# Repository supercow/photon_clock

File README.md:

# Photon Clock

This repository contains all of the software and schematics required to build
and flash a 16x2 smart clock driven by a [Particle Photon](https://store.particle.io/#photon).

## Parts list

- PCB (see below for details)
- [HD44780 assembled LCD](https://www.adafruit.com/products/1447)
- Trim potentiometer (should come with the HD44780)
- [TMP36 temperature sensor](https://www.adafruit.com/products/165) (not needed if using external weather)
- [Particle Photon with headers](https://store.particle.io/#photon)
- ~50-60ohm THT resistor
- 10nF capacitor

### 3D printed enclosure
- Enclosure itself (see below for details)
- 4x M2x20mm machine screws
- 4x M2 nuts
- [Optional] 30mm cooling fan (requires fasteners and electrical tape)
- [Optional] Self-adhesive velcro strips

## PCB details

Eagle 8 format schematics are included in the "eagle" directory in this
repository. If you wish to order a PCB, you will need to use a service that
supports Eagle .brd files, or generate your own Gerbers.

I recommend [OSH Park](https://www.oshpark.com/) for ease of use, cost, quality,
and their cool purple soldermask. You can order this board directly with [this](https://www.oshpark.com/orders/cart)
link.

## 3D printed enclosure details

Autodesk Fusion 360 source files and printable STL files are included in the "enclosure" directory in this repository.

### Assembly notes
* Print using 100% infill; no supports necessary.
* If using a cooling fan, cover the top of the partition that separates the Photon board from the temperature sensor with electrical tape. This will create a seal between the enclosure bottom and the PCB to block pushed air from impacting temperature readings. Fan is intended to be mounted externally using the mounting holes on the enclosure bottom.
* Enclosure is intended to be mounted under a computer monitor with velcro but works just fine unmounted. Velcro should be adhered to the enclosure side without the honeycomb cutouts.

## Building the software

### Pre-requisites

- A registered, Wi-Fi enabled Photon, ideally already connected
- The Particle IDE or command line tools installed and configured
- If you wish to use the command line version, a \*nix compatible shell is
  required

See instructions in the `code/build.sh` script to build and flash the Photon via
the command line. To flash via the Particle Atom IDE, open the project in `code`
and flash as usual.

If you wish to use the built-in temperature sensor, you will need to comment out
the following line:

`#define EXTERNAL_TEMP true`

## External integrations

In order for the clock to set the correct timezone, you will need to configure
the `timezone.json` external integration in the `integrations` directory in the
Particle console.

In order for the clock to collect external weather, you will need to configure
the `weather.json` external integration.

**Please note** that you must supply your own API key or none of the
integrations will work.

To configure each custom integration:
1. Go to [https://console.particle.io/integrations](https://console.particle.io/integrations) in your web browser
1. Click "NEW INTEGRATION"
1. Click "Webhook", then "Custom JSON"
1. Paste the contents of the relevant `.json` file from the `integrations`
   directory
1. Edit the URL section to include your API key
1. Click "CREATE WEBHOOK"

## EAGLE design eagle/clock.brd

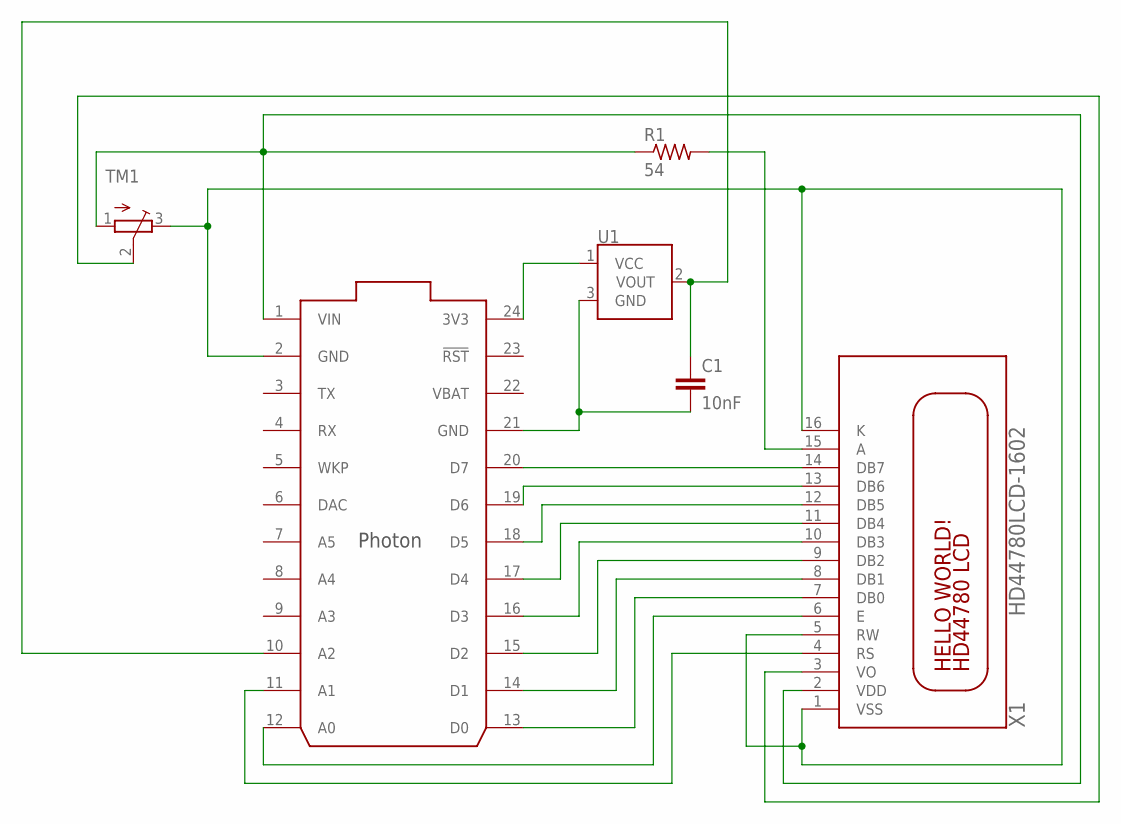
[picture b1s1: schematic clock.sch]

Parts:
C1: 10nF; CAP-PTH-10MM
R1: 54; 0309/12
TM1: TRIMPOT3386; TRIM-3386
U1: TMP36GT9; TO-92
U$1: PHOTON_WITH_HEADERS; PHOTON
X1: HD44780LCD-1602; LCD1602

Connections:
unnamed: U$1.19 (D6), X1.13 (DB6)
unnamed: C1.1, U1.2 (VOUT), U$1.10 (A2)
unnamed: U$1.12 (A0), X1.6 (E)
unnamed: U$1.18 (D5), X1.12 (DB5)
unnamed: U$1.17 (D4), X1.11 (DB4)
unnamed: U$1.20 (D7), X1.14 (DB7)
unnamed: U$1.16 (D3), X1.10 (DB3)
unnamed: U$1.15 (D2), X1.9 (DB2)
unnamed: U$1.14 (D1), X1.8 (DB1)
unnamed: U$1.13 (D0), X1.7 (DB0)
unnamed: U$1.11 (A1), X1.4 (RS)
unnamed: R1.2, X1.15 (A)
unnamed: TM1.2 (S), X1.3 (VO)
unnamed: U1.1 (VCC), U$1.24 (3V3)
unnamed: C1.2, U1.3 (GND), U$1.21 (GND)
VBAT: U$1.22 (VBAT)
VDD: R1.1, TM1.1 (A), U$1.1 (VIN), X1.2 (VDD)
VSS: TM1.3 (E), U$1.2 (GND), X1.1 (VSS), X1.5 (RW), X1.16 (K)

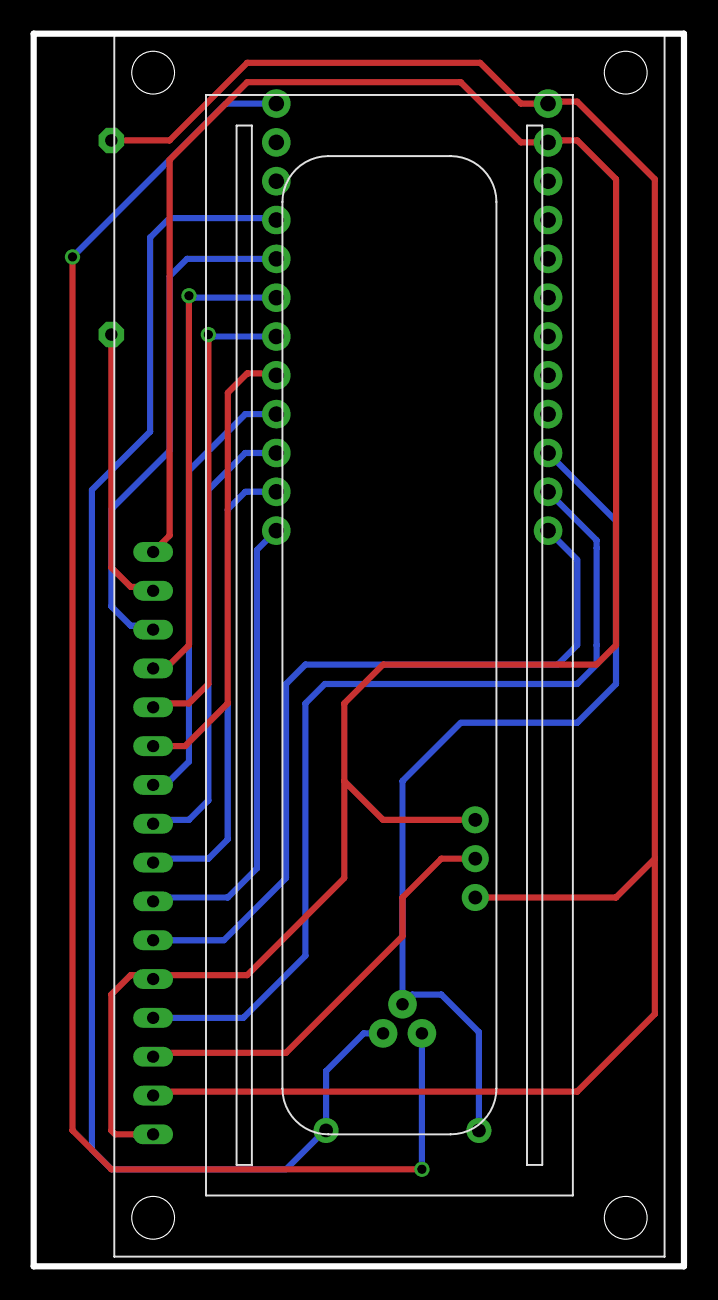
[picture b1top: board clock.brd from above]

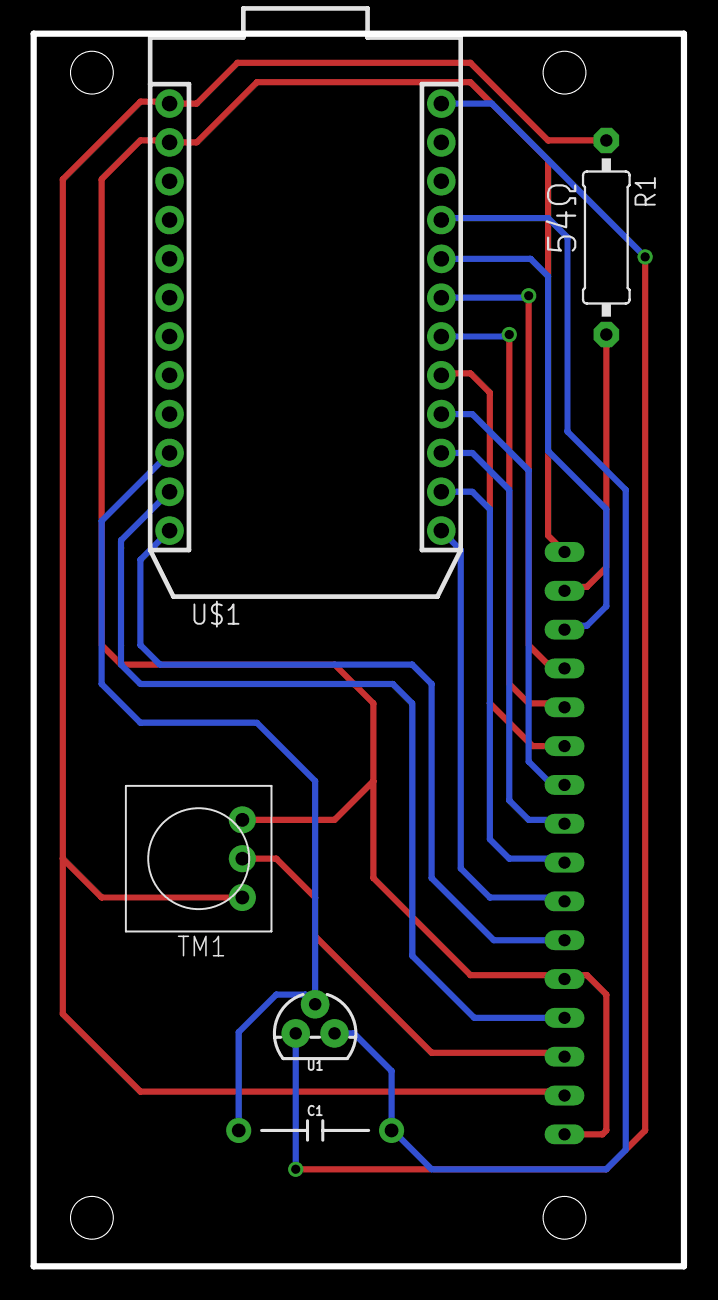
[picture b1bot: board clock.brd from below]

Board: 2 copper layers, 42.5 x 80.6 mm, 6 parts (5 on the bottom side), 17 nets.

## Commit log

2017-03-19 First pass rest client
2017-03-19 Change rest to timezonedb.com
2017-03-19 trying and failing to get timezone sync working
2017-03-19 Uh, stuff.
2017-03-20 Add external weather
2017-03-25 Document build script
2017-03-25 Reorganize
2017-03-25 Add eagle files
2017-03-25 Add integration configuration
2017-03-25 Add integration instructions
2017-03-25 Clarified software instructions
2017-03-25 Add OSH park order link
2017-04-26 Added 3D printed enclosure and updated readme.
2017-04-26 Fixed number of screws in readme.
2017-04-26 Updated top-bottom rendering; fixed some text.
2017-04-26 Updated model orientation to allow for printing without supports.
2017-04-27 Updated readme w/ velcro notes; added new renderings of assembled unit (minus screws).
2017-07-15 Add restart if weather does not update for 4*interval

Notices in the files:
parts and their libraries:
SparkFun-Sensors: Licensing: Creative Commons ShareAlike 4.0 International - https://creativecommons.org/licenses/by-sa/4.0
